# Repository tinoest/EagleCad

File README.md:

View this project on [CADLAB.io](https://cadlab.io/project/1018). 

EagleCad
========

Various Schematics

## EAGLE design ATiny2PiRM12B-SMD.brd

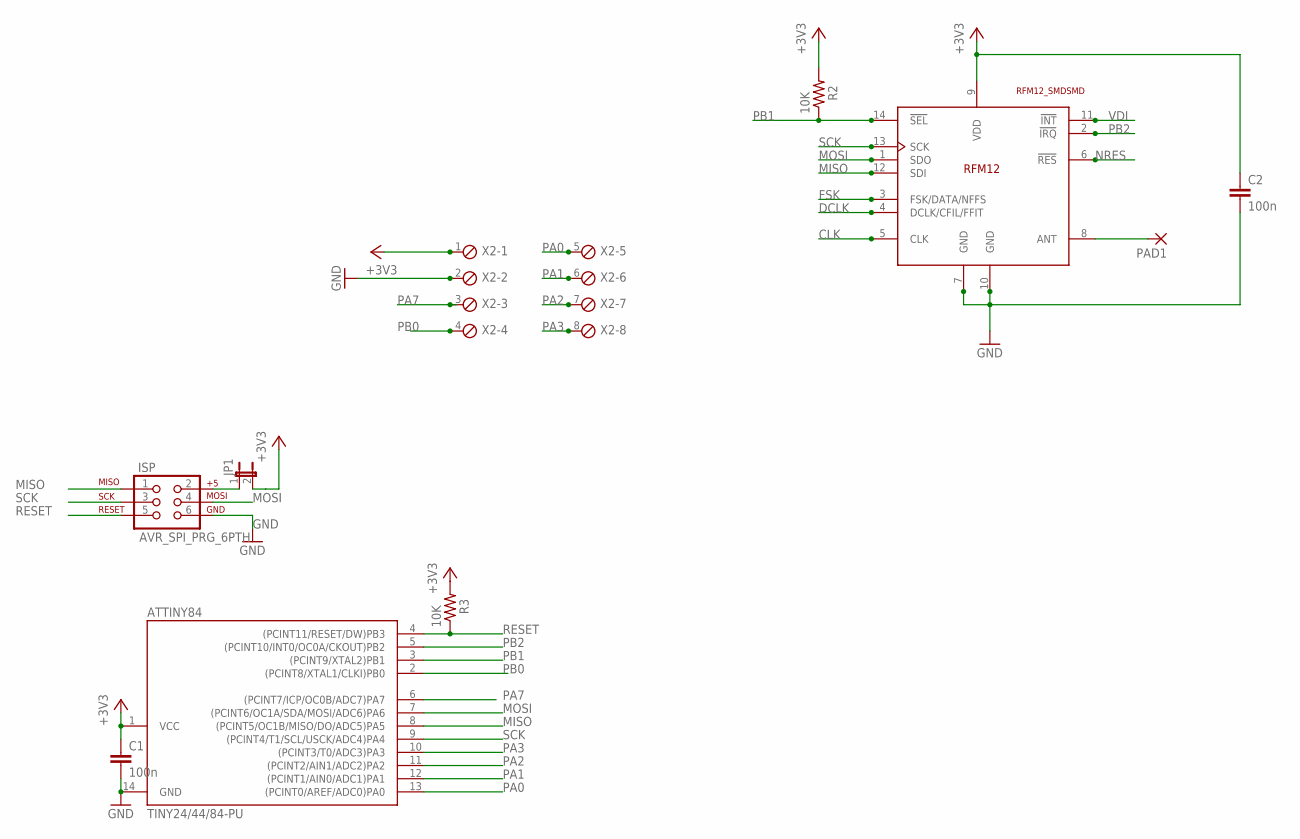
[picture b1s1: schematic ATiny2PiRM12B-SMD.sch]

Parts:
ATTINY84: TINY24/44/84-PU; DIL14
C1, C2: 100n; C025-024X044
ISP: AVR_SPI_PRG_6PTH; 2X3
JP1: JUMPER-2PTH; 1X02
PAD1: 1,6/0,8
R2, R3: 10K; AXIAL-0.3
U$2: RFM12_SMDSMD; RFM12
X2: MPT8; 8POL254

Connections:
+3V3: ATTINY84.1 (VCC), C1.1, JP1.2, R2.P$2 (2), R3.P$2 (2), X2.1
CLK: U$2.5 (CLK)
DCLK: U$2.4 (DCLK/CFIL/FFIT)
FSK: U$2.3 (FSK/DATA/NFFS)
GND: ATTINY84.14 (GND), C1.2, C2.2, ISP.6, U$2.7 (GND), U$2.10 (GND), X2.2
MISO: ATTINY84.8 ((PCINT5/OC1B/MISO/DO/ADC5)PA5), ISP.1, U$2.12 (SDI)
MOSI: ATTINY84.7 ((PCINT6/OC1A/SDA/MOSI/ADC6)PA6), ISP.4, U$2.1 (SDO)
unnamed: ISP.2, JP1.1
unnamed: PAD1.1, U$2.8 (ANT)
NRES: U$2.6 (!RES)
PA0: ATTINY84.13 ((PCINT0/AREF/ADC0)PA0), X2.5
PA1: ATTINY84.12 ((PCINT1/AIN0/ADC1)PA1), X2.6
PA2: ATTINY84.11 ((PCINT2/AIN1/ADC2)PA2), X2.7
PA3: ATTINY84.10 ((PCINT3/T0/ADC3)PA3), X2.8
PA7: ATTINY84.6 ((PCINT7/ICP/OC0B/ADC7)PA7), X2.3
PB0: ATTINY84.2 ((PCINT8/XTAL1/CLKI)PB0), X2.4
PB1: ATTINY84.3 ((PCINT9/XTAL2)PB1), R2.P$1 (1), U$2.14 (!SEL)
PB2: ATTINY84.5 ((PCINT10/INT0/OC0A/CKOUT)PB2), U$2.2 (!IRQ)
RESET: ATTINY84.4 ((PCINT11/RESET/DW)PB3), ISP.5, R3.P$1 (1)
SCK: ATTINY84.9 ((PCINT4/T1/SCL/USCK/ADC4)PA4), ISP.3, U$2.13 (SCK)
VDD: C2.1, U$2.9 (VDD)
VDI: U$2.11 (!INT)

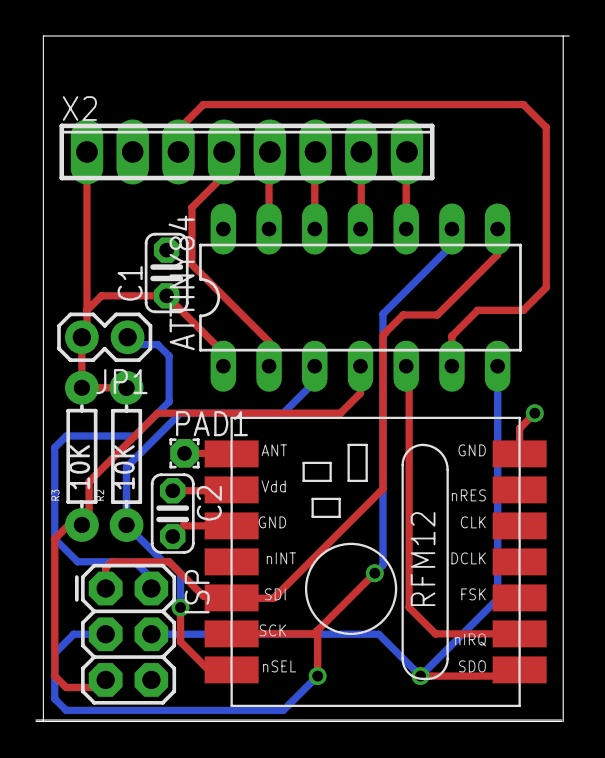
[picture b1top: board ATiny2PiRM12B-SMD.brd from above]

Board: 2 copper layers, 29.6 x 38.1 mm, 10 parts (0 on the bottom side), 17 nets.

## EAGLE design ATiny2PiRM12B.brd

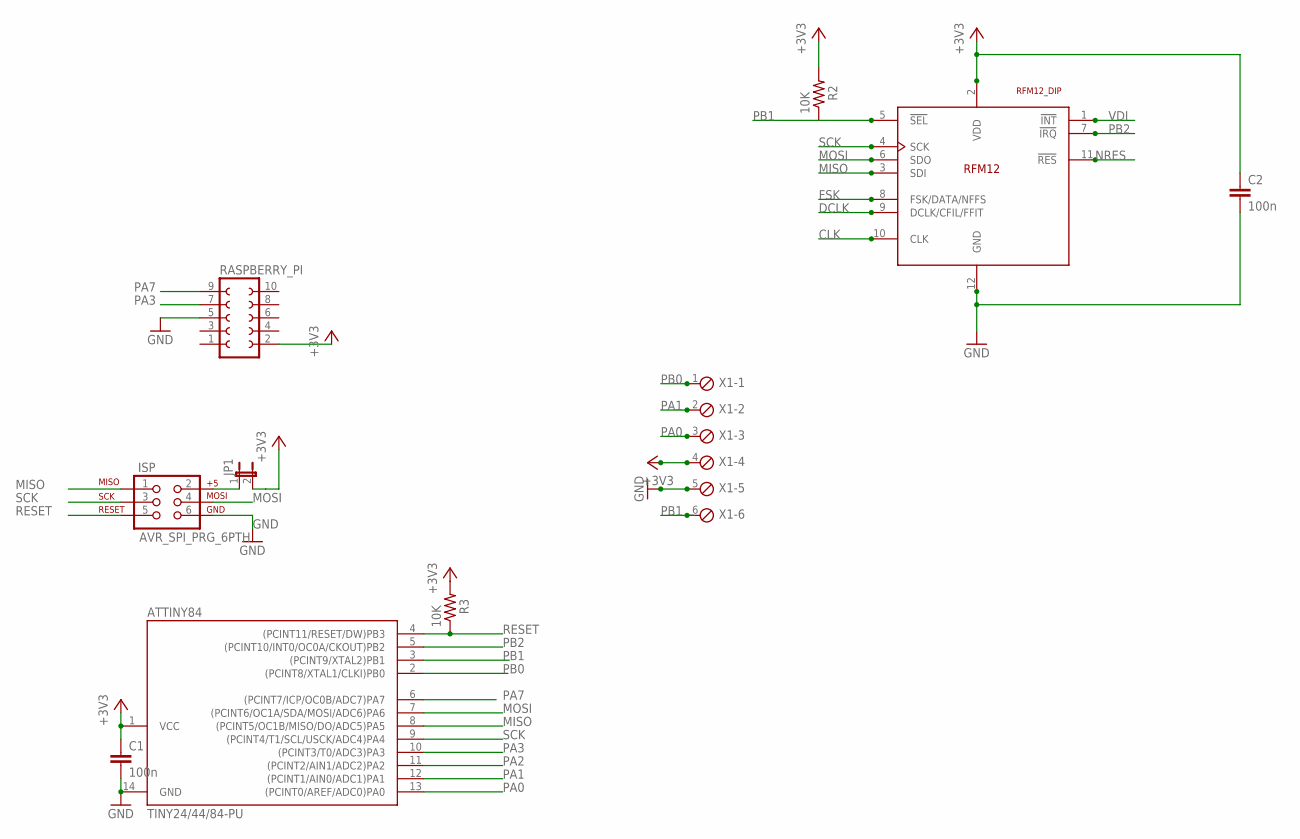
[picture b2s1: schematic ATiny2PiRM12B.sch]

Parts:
ATTINY84: TINY24/44/84-PU; DIL14
C1, C2: 100n; C025-024X044
ISP: AVR_SPI_PRG_6PTH; 2X3
JP1: JUMPER-2PTH; 1X02
R2, R3: 10K; AXIAL-0.3
RASPBERRY_PI: FE05-2
U$1: RFM12_DIP; DIL-2MM-2X06
X1: MPT6; 6POL254

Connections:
+3V3: ATTINY84.1 (VCC), C1.1, C2.1, JP1.2, R2.P$2 (2), R3.P$2 (2), RASPBERRY_PI.2, U$1.2 (VDD), X1.4
CLK: U$1.10 (CLK)
DCLK: U$1.9 (DCLK/CFIL/FFIT)
FSK: U$1.8 (FSK/DATA/NFFS)
GND: ATTINY84.14 (GND), C1.2, C2.2, ISP.6, RASPBERRY_PI.5, U$1.12 (GND), X1.5
MISO: ATTINY84.8 ((PCINT5/OC1B/MISO/DO/ADC5)PA5), ISP.1, U$1.3 (SDI)
MOSI: ATTINY84.7 ((PCINT6/OC1A/SDA/MOSI/ADC6)PA6), ISP.4, U$1.6 (SDO)
unnamed: ISP.2, JP1.1
NRES: U$1.11 (!RES)
PA0: ATTINY84.13 ((PCINT0/AREF/ADC0)PA0), X1.3
PA1: ATTINY84.12 ((PCINT1/AIN0/ADC1)PA1), X1.2
PA2: ATTINY84.11 ((PCINT2/AIN1/ADC2)PA2)
PA3: ATTINY84.10 ((PCINT3/T0/ADC3)PA3), RASPBERRY_PI.7
PA7: ATTINY84.6 ((PCINT7/ICP/OC0B/ADC7)PA7), RASPBERRY_PI.9
PB0: ATTINY84.2 ((PCINT8/XTAL1/CLKI)PB0), X1.1
PB1: ATTINY84.3 ((PCINT9/XTAL2)PB1), R2.P$1 (1), U$1.5 (!SEL), X1.6
PB2: ATTINY84.5 ((PCINT10/INT0/OC0A/CKOUT)PB2), U$1.7 (!IRQ)
RESET: ATTINY84.4 ((PCINT11/RESET/DW)PB3), ISP.5, R3.P$1 (1)
SCK: ATTINY84.9 ((PCINT4/T1/SCL/USCK/ADC4)PA4), ISP.3, U$1.4 (SCK)
VDI: U$1.1 (!INT)

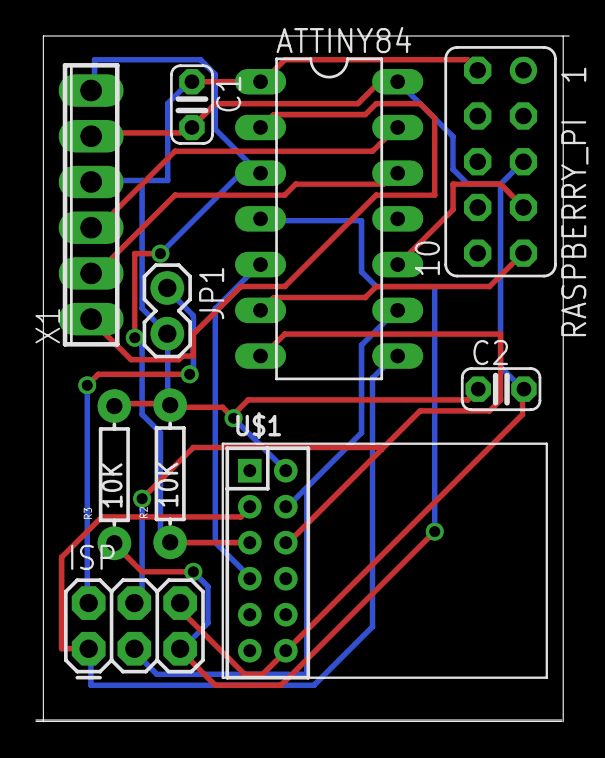
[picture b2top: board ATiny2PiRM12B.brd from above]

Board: 2 copper layers, 29.6 x 38.1 mm, 10 parts (0 on the bottom side), 14 nets.

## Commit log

2014-05-11 Initial Version Release
2014-05-11 Create LICENCE
2015-03-23 Checking in new board design and lb.
2018-05-11 Backlink to CADLAB.io has been added.
